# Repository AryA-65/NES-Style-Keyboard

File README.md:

# NES-Style-Keyboard
- - - -

## Notice
- - - -
> [!IMPORTANT]  
> It is always advised that you review the files before ordering, as there may be small issues with the current revision.

## Description
- - - -
A friend of mine wanted to buy a keyboard. I convinced him to let me build him one. I decided to build him a custom 75% keyboard, with some extra features based on his preferences, and styled the color scheme to the popular NES. The whole keyboard, including the case, the main PCB, the switch plate and some of the caps, are custom designed by me.

## Gallery

## Features
- - - -
* Sliding Potentiometer
  * One of my friend's requests was to cater the keyboard more towards CAD design. The only right solution, in my opinion, is a sliding potentiometer for zoom control in apps like Fusion. To zoom using the slider, hold CTRL and move the slider up or down. To scroll horizontally, hold SHIFT and move the slider up or down.
* Rotary Encoder
  * The rotary encoder serves as playback control (play/pause/previous/skip), but also as volume control. If volume control is already mapped by the potentiometer, the encoder can serve to switch audio channels controlled by the potentiometer (ex: switching from the music media channel to the system audio channel)
* Addressable RGB LEDs
  * A total of 6 WS2812b leds are included on the left hand side of the keyboard, right next to the sliding potentiometer. They indicate volume level (if controlled by the potentiometer) and/or caps lock.
* Repairable Design
  * The power supplied to the main PCB comes from a small daughterboard at the back, middle of the case. This daughterboard consists of a 3V3 LDO as well as a fuse. The two PCBs are connected through a standard 15cm (0.5ft) USB-C cable, allowing for easy replacement by the user.
* Unibody Body Case
  * The case for the keyboard is as a unibody case. It is built to offer comfort, whilst keeping a thocky sound (it does sound awesome).
* Hot Swappable Keyswitches
  * Does this need to be explain at this point?

## Default keymaps
```
# Base Layer
[_BASE] = LAYOUT(
        KC_ESC, KC_F1, KC_F2, KC_F3, KC_F4, KC_F5, KC_F6, KC_F7, KC_F8, KC_F9, KC_F10, KC_F11, KC_F12, KC_HOME, KC_END, KC_PAUSE,
        KC_GRV, KC_1, KC_2, KC_3, KC_4, KC_5, KC_6, KC_7, KC_8, KC_9, KC_0, KC_MINS, KC_EQL,                    KC_BSPC, KC_INS,
        KC_TAB,     KC_Q, KC_W, KC_E, KC_R, KC_T, KC_Y, KC_U, KC_I, KC_O, KC_P, KC_LBRC, KC_RBRC,               KC_BSLS, KC_DEL,
        KC_CAPS,        KC_A, KC_S, KC_D, KC_F, KC_G, KC_H, KC_J, KC_K, KC_L, KC_SCLN, KC_QUOT,                 KC_ENT, KC_PGUP,
        KC_LSFT,            KC_Z, KC_X, KC_C, KC_V, KC_B, KC_N, KC_M, KC_COMM, KC_DOT, KC_SLSH, KC_RSFT,        KC_UP, KC_PGDN,
        KC_LCTL,    KC_LGUI,    KC_LALT,            KC_SPC,                   KC_RALT, MO(_FL), KC_RCTL, KC_LEFT, KC_DOWN, KC_RIGHT
    )

#Fn Layer
[_FL] = LAYOUT(
        _______, KC_PWR, KC_F2, KC_BRIU, KC_BRID, KC_F5, KC_MSEL, KC_F7, KC_F8, KC_F9, KC_F10, KC_F11, KC_F12, _______, _______, KC_SLEP,
        _______, _______, _______, _______, _______, _______, _______, _______, _______, _______, _______, UG_SPDD, UG_SPDU,              _______, UG_NEXT,
        _______, _______, _______, _______, _______, _______, _______, _______, _______, _______, _______, _______, _______, _______, UG_PREV,
        _______, _______, _______, _______, _______, _______, _______, _______, _______, _______, _______, _______,     _______, UG_SATU,
        _______, _______, _______, _______, _______, _______, _______, _______, _______, _______, _______, _______,     UG_VALU, UG_SATD,
        _______,    _______,    _______,            _______,                    _______, _______, _______, UG_HUED, UG_VALD, UG_HUEU
    )
```

## Parts List
- - - -
|Part|*Price|*Shipping|Link|
|----|-----------|--------|----|
|Keycaps|$34.18|NaN|[XDA Retro NES Keycaps](https://www.aliexpress.com/item/1005007393936770.html?spm=a2g0o.order_list.order_list_main.25.587f1802SPZi3h)|
|Keyswitches (90pcs)|$32.18|NaN|[MMD Cream Switches (45G)](https://www.aliexpress.com/item/1005007083480212.html?spm=a2g0o.order_list.order_list_main.35.587f1802SPZi3h)|
|Hotswap Sockets (110ps)|$12.21|NaN|[110pcs Kailh Hot-swappable Sockets](https://www.aliexpress.com/item/1005007232040760.html?spm=a2g0o.order_list.order_list_main.30.587f1802SPZi3h)|
|Diodes|$3.17|NaN|[100pcs 1N4148W](https://www.aliexpress.com/item/1005009660071572.html?spm=a2g0o.order_list.order_list_main.20.587f1802SPZi3h)|
|Stabilizers|$25.99|NaN|[Durock Screw in Stabilizers V3 (Black)](https://www.aliexpress.com/item/1005003682325989.html?spm=a2g0o.order_list.order_list_main.10.587f1802SPZi3h)|
|USB-C Cable|$12.64|NaN|[6 inch USB C to USB C Cable (3 Pack)](https://www.amazon.ca/dp/B0CLLRBZDB)|
|BOM|$34.96|$8.00|[BOMs](production_files)|
|Main PCB|$31.20|$43.78**|[Main PCB](production_files/gerbers_to_order_main)|
|Daughterboard|$3.00|$43.78**|[Daughterboard PCB](production_files/gerbers_to_order_secondary)|
|Switch Plate****|$0.00|NaN|[Plate PCB](production_files/gerbers_to_order_plate)|
|Case|$65.13|$43.78**|[Enclosure](production_files/3D_files/)|
|Misc.|$6.50***|$43.78**|[Misc. Parts](production_files/3D_files/)|

Total (excluding import fees): $298.66

*All prices are in CAD, check in your own currency before buying.
**Combined shipping for keyboard and daughterboard PCB, misc. items and enclosure.
***Includes encoder knob, slider handle, power led bar and status bar
****I decided to print the switchplate at home, since it was much cheaper per unit and overall compared to ordering it (price will be updated soon).

## Quickstart
- - - -
### 1) First flash
This step if for first flash, right after assembling your PCBs:
1) Download the UF2 prebuilt firmware in [firmware](firmware/).
2) Connect main board to daughterboard through USB-C intercable (**never connect a USB-C cable directly to the main PCB, it will damage the board**).
3) Press and hold EN button on keyboard.
4) Plug USB-C cable from computer to daughterboard, and let go of the EN button.
5) A USB device will appear in your file explorer, drag and drop UF2 file from your downloads folder into the USB device.
6) If the keyboard automatically resets, the flash was successful. Otherwise, try flashing again.

### 2) Reflash
Since the EN button is on the opposite side of the board and not accessible once the keyboard is assembled, I added a key combo that resets the board and enables flashing new firmware:
1) Press and release right CTRL, ESC, left CTRL and END button at the same time.
2) Drag and drop UF2 firmware from your computer onto the keyboard.
3) If the keyboard automatically resets, the flash was successful. Otherwise, try flashing again (step 1).

## Support
- - - -
Coming Soon

## Tools Used
- - - -
- [Kicad](https://www.kicad.org/)
- [Keyboard Layout Editor](https://www.keyboard-layout-editor.com/#/)
- [Autodesk Fusion](https://www.autodesk.com/products/fusion-360/overview)
- [QMK Firmawre](https://qmk.fm/)

## Legal Notice
- - - -
The software and hardware come as is. It is up to the user to review and make sure that they understand the scope of the project before attempting the project.
[GPL V2 License](LICENSE)

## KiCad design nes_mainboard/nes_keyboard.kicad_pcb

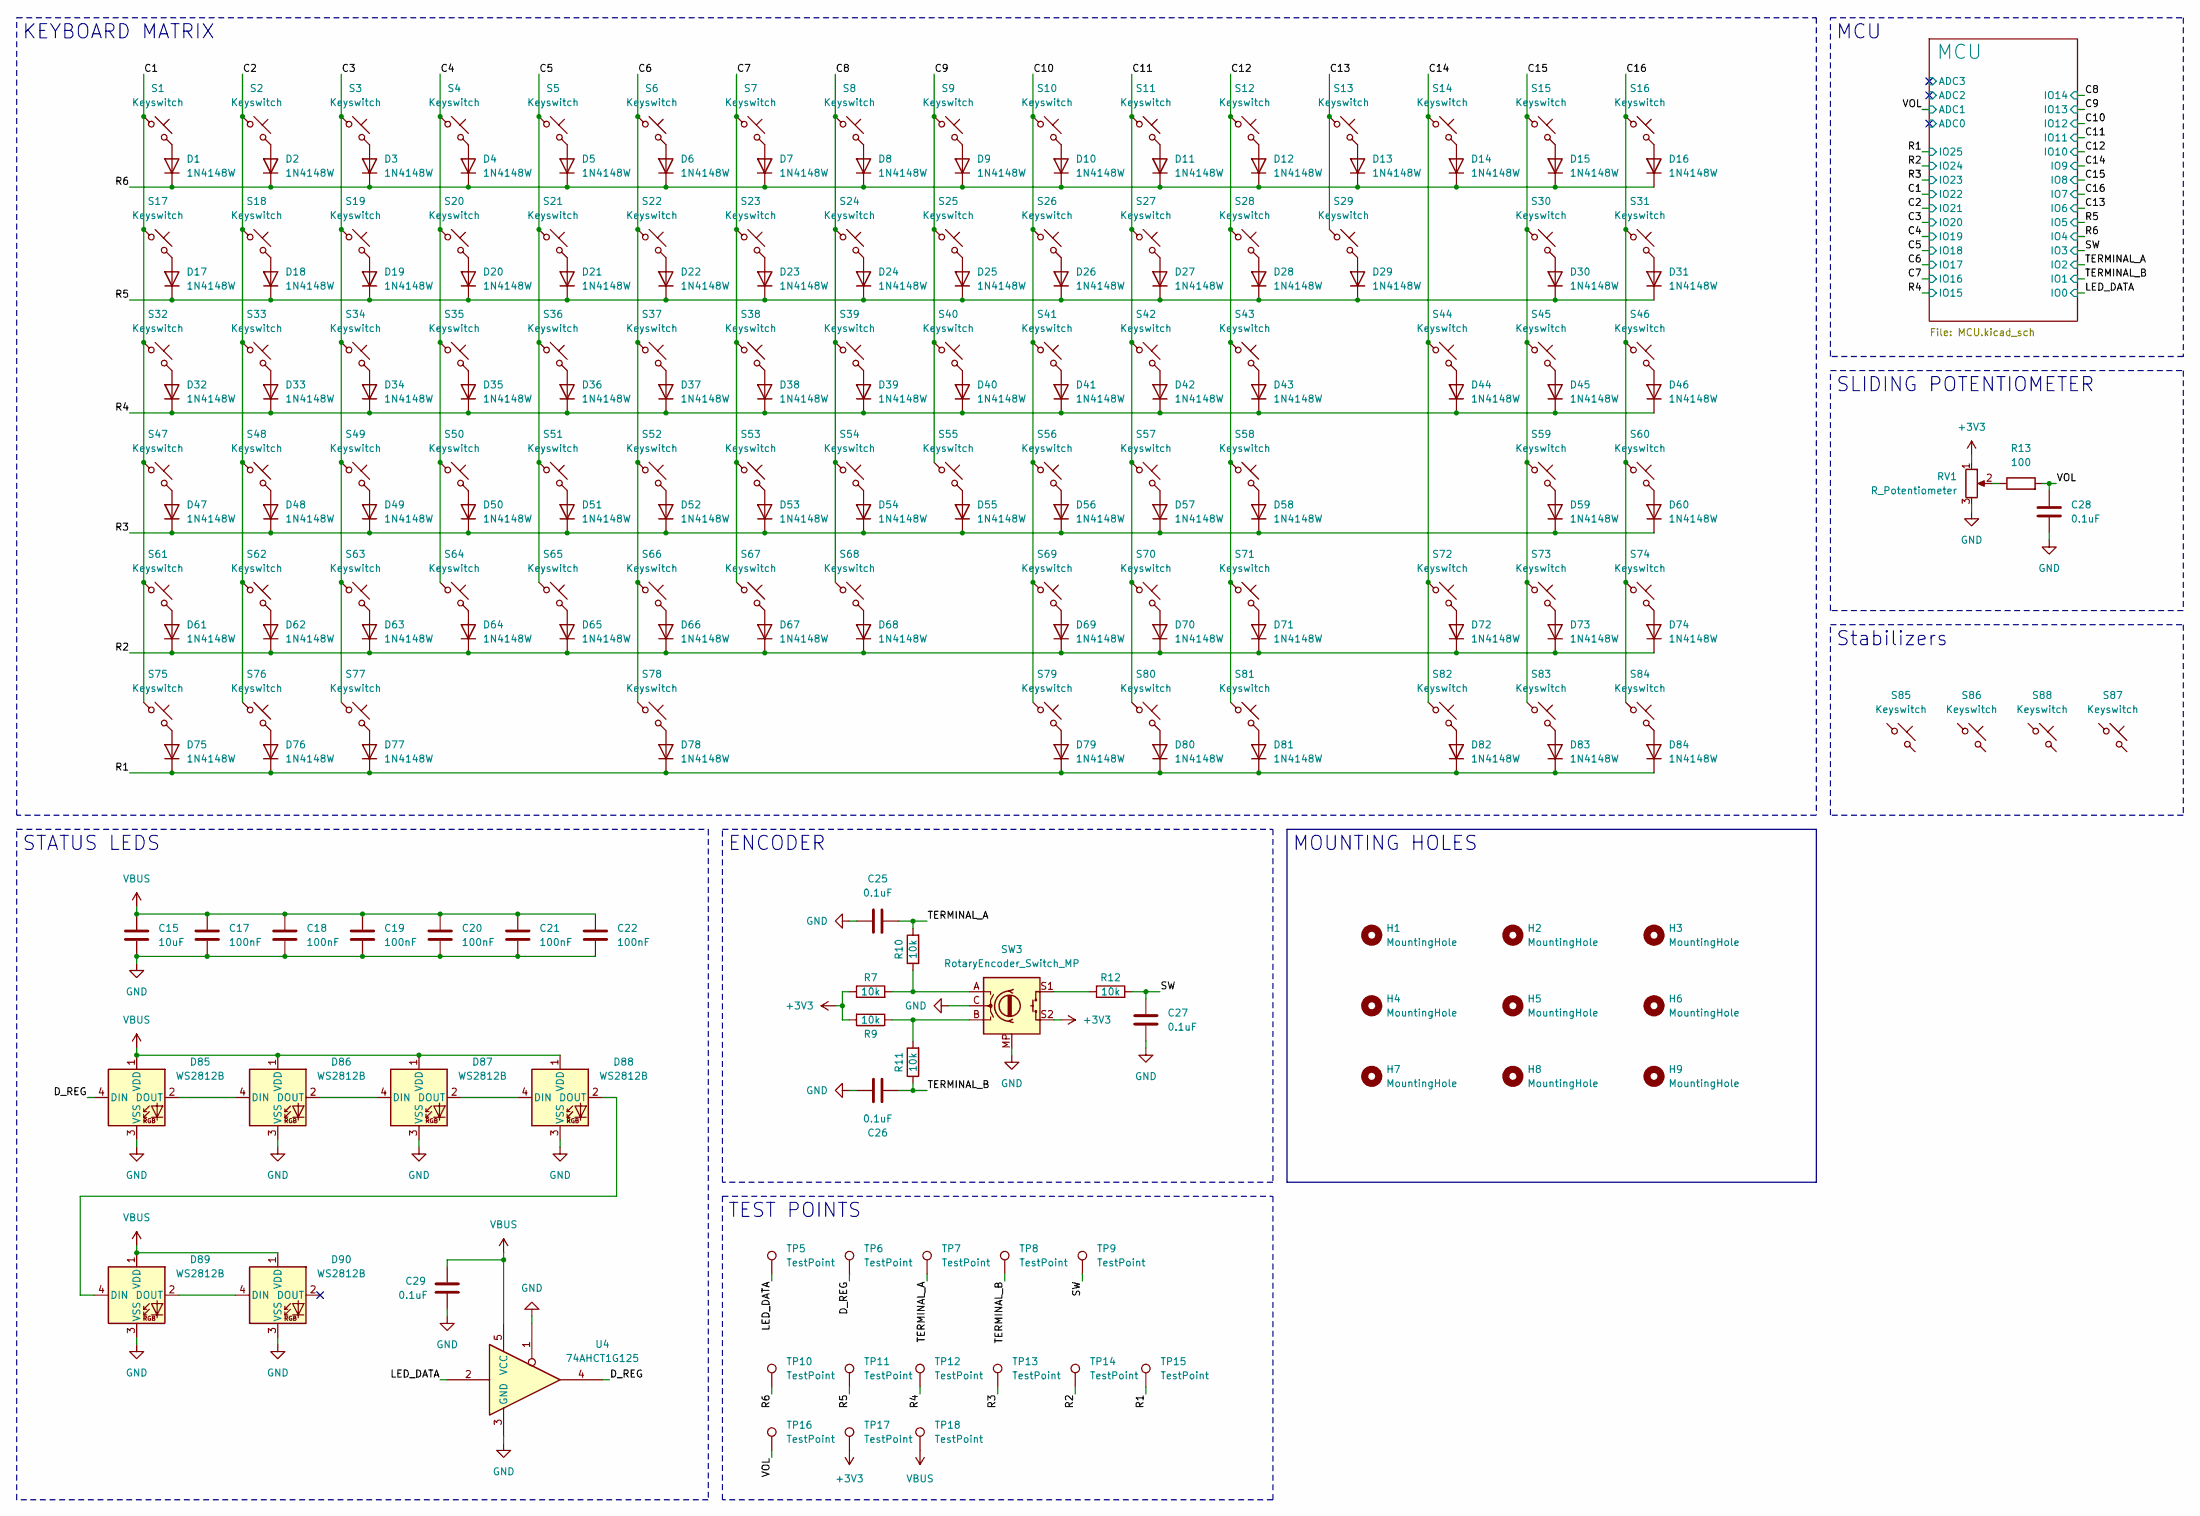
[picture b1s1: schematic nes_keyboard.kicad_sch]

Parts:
C15: 10uF; C_0805_2012Metric; Part Num. CL21A106KOQNNNE
C17, C18, C19, C20, C21, C22: 100nF; C_0603_1608Metric; Part Num. CL10B104KO8NNNC
C25, C26, C27, C28, C29: 0.1uF; C_0402_1005Metric; Part Num. CL05B104KP5NNNC
D1, D2, D3, D4, D5, D6, D7, D8, D9, D10, D11, D12, D13, D14, D15, D16, D17, D18, D19, D20, D21, D22, D23, D24, D25, D26, D27, D28, D29, D30, D31, D32, D33, D34, D35, D36, D37, D38, D39, D40, D41, D42, D43, D44, D45, D46, D47, D48, D49, D50, D51, D52, D53, D54, D55, D56, D57, D58, D59, D60, D61, D62, D63, D64, D65, D66, D67, D68, D69, D70, D71, D72, D73, D74, D75, D76, D77, D78, D79, D80, D81, D82, D83, D84: 1N4148W; D_SOD-123; Part Num. 1N4148W
D85, D86, D87, D88, D89, D90: WS2812B; LED_WS2812B-4020
H1, H2, H3, H4, H5, H6, H7, H8, H9: MountingHole; MountingHole_2.2mm_M2_Pad
R7, R9, R10, R11, R12: 10k; R_0402_1005Metric; Part Num. RMCF0402FT10K0
R13: 100; R_0603_1608Metric; Part Num. RC0603FR-07100RL
RV1: R_Potentiometer; TRIM_PTA6043-2015DPB103; Part Num. PTA6043-2010CIB103
S1, S2, S3, S4, S5, S6, S7, S8, S9, S10, S11, S12, S13, S14, S15, S16, S17, S18, S19, S20, S21, S22, S23, S24, S25, S26, S27, S28, S29, S31, S33, S34, S35, S36, S37, S38, S39, S40, S41, S42, S43, S44, S46, S48, S49, S50, S51, S52, S53, S54, S55, S56, S57, S58, S60, S62, S63, S64, S65, S66, S67, S68, S69, S70, S71, S73, S74, S79, S80, S81, S82, S83, S84: Keyswitch; Hotswap_MX_1.00u
S30: Keyswitch; Hotswap_MX_2.00u
S32, S45: Keyswitch; Hotswap_MX_1.50u
S47, S72: Keyswitch; Hotswap_MX_1.75u
S59, S61: Keyswitch; Hotswap_MX_2.25u
S75, S76, S77: Keyswitch; Hotswap_MX_1.25u
S78: Keyswitch; Hotswap_MX_6.25u
S85, S86, S87: Keyswitch; Stabilizer_Cherry_MX_2.00u
S88: Keyswitch; Stabilizer_Cherry_MX_6.25u
SW3: RotaryEncoder_Switch_MP; RotaryEncoder_Bourns_Vertical_PEC12R-3x17F-Sxxxx; Part Num. PEC12R-4217F-S0024
TP5, TP6, TP7, TP8, TP9, TP10, TP11, TP12, TP13, TP14, TP15, TP16, TP17, TP18: TestPoint; TestPoint_Pad_D1.0mm
U4: 74AHCT1G125; SOT-23-5_HandSoldering; Part Num. SN74AHCT1G125DBVR

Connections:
+3V3: R7.1, R9.2, RV1.1, SW3.S2, TP17.1 (1_1); also elsewhere on the board
/C1: S1.1, S17.1, S32.1, S47.1, S61.1, S75.1; also elsewhere on the board
/C2: S2.1, S18.1, S33.1, S48.1, S62.1, S76.1; also elsewhere on the board
/C3: S3.1, S19.1, S34.1, S49.1, S63.1, S77.1; also elsewhere on the board
/C4: S4.1, S20.1, S35.1, S50.1, S64.1; also elsewhere on the board
/C5: S5.1, S21.1, S36.1, S51.1, S65.1; also elsewhere on the board
/C6: S6.1, S22.1, S37.1, S52.1, S66.1, S78.1; also elsewhere on the board
/C7: S7.1, S23.1, S38.1, S53.1, S67.1; also elsewhere on the board
/C8: S8.1, S24.1, S39.1, S54.1, S68.1; also elsewhere on the board
/C9: S9.1, S25.1, S40.1, S55.1; also elsewhere on the board
/C10: S10.1, S26.1, S41.1, S56.1, S69.1, S79.1; also elsewhere on the board
/C11: S11.1, S27.1, S42.1, S57.1, S70.1, S80.1; also elsewhere on the board
/C12: S12.1, S28.1, S43.1, S58.1, S71.1, S81.1; also elsewhere on the board
/C13: S13.1, S29.1; also elsewhere on the board
/C14: S14.1, S44.1, S72.1, S82.1; also elsewhere on the board
/C15: S15.1, S30.1, S45.1, S59.1, S73.1, S83.1; also elsewhere on the board
/C16: S16.1, S31.1, S46.1, S60.1, S74.1, S84.1; also elsewhere on the board
/D_REG: D85.4 (DIN), TP6.1 (1_1), U4.4
/LED_DATA: TP5.1 (1_1), U4.2; also elsewhere on the board
/R1: D75.1 (K), D76.1 (K), D77.1 (K), D78.1 (K), D79.1 (K), D80.1 (K), D81.1 (K), D82.1 (K), D83.1 (K), D84.1 (K), TP15.1 (1_1); also elsewhere on the board
/R2: D61.1 (K), D62.1 (K), D63.1 (K), D64.1 (K), D65.1 (K), D66.1 (K), D67.1 (K), D68.1 (K), D69.1 (K), D70.1 (K), D71.1 (K), D72.1 (K), D73.1 (K), D74.1 (K), TP14.1 (1_1); also elsewhere on the board
/R3: D47.1 (K), D48.1 (K), D49.1 (K), D50.1 (K), D51.1 (K), D52.1 (K), D53.1 (K), D54.1 (K), D55.1 (K), D56.1 (K), D57.1 (K), D58.1 (K), D59.1 (K), D60.1 (K), TP13.1 (1_1); also elsewhere on the board
/R4: D32.1 (K), D33.1 (K), D34.1 (K), D35.1 (K), D36.1 (K), D37.1 (K), D38.1 (K), D39.1 (K), D40.1 (K), D41.1 (K), D42.1 (K), D43.1 (K), D44.1 (K), D45.1 (K), D46.1 (K), TP12.1 (1_1); also elsewhere on the board
/R5: D17.1 (K), D18.1 (K), D19.1 (K), D20.1 (K), D21.1 (K), D22.1 (K), D23.1 (K), D24.1 (K), D25.1 (K), D26.1 (K), D27.1 (K), D28.1 (K), D29.1 (K), D30.1 (K), D31.1 (K), TP11.1 (1_1); also elsewhere on the board
/R6: D1.1 (K), D2.1 (K), D3.1 (K), D4.1 (K), D5.1 (K), D6.1 (K), D7.1 (K), D8.1 (K), D9.1 (K), D10.1 (K), D11.1 (K), D12.1 (K), D13.1 (K), D14.1 (K), D15.1 (K), D16.1 (K), TP10.1 (1_1); also elsewhere on the board
/SW: C27.1, R12.2, TP9.1 (1_1); also elsewhere on the board
/TERMINAL_A: C25.2, R10.2, TP7.1 (1_1); also elsewhere on the board
/TERMINAL_B: C26.1, R11.1, TP8.1 (1_1); also elsewhere on the board
/VOL: C28.2, R13.2, TP16.1 (1_1); also elsewhere on the board
GND: C15.2, C17.2, C18.2, C19.2, C20.2, C21.2, C22.2, C25.1, C26.2, C27.2, C28.1, C29.2, D85.3 (VSS), D86.3 (VSS), D87.3 (VSS), D88.3 (VSS), D89.3 (VSS), D90.3 (VSS), RV1.3, SW3.C, SW3.MP, U4.1, U4.3 (GND); also elsewhere on the board
unnamed: D1.2 (A), S1.2
unnamed: D2.2 (A), S2.2
unnamed: D3.2 (A), S3.2
unnamed: D4.2 (A), S4.2
unnamed: D5.2 (A), S5.2
unnamed: D6.2 (A), S6.2
unnamed: D7.2 (A), S7.2
unnamed: D8.2 (A), S8.2
unnamed: D9.2 (A), S9.2
unnamed: D10.2 (A), S10.2
unnamed: D11.2 (A), S11.2
unnamed: D12.2 (A), S12.2
unnamed: D13.2 (A), S13.2
unnamed: D14.2 (A), S14.2
unnamed: D15.2 (A), S15.2
unnamed: D16.2 (A), S16.2
unnamed: D17.2 (A), S17.2
unnamed: D18.2 (A), S18.2
unnamed: D19.2 (A), S19.2
unnamed: D20.2 (A), S20.2
unnamed: D21.2 (A), S21.2
unnamed: D22.2 (A), S22.2
unnamed: D23.2 (A), S23.2
unnamed: D24.2 (A), S24.2
unnamed: D25.2 (A), S25.2
unnamed: D26.2 (A), S26.2
unnamed: D27.2 (A), S27.2
unnamed: D28.2 (A), S28.2
unnamed: D29.2 (A), S29.2
unnamed: D30.2 (A), S30.2
unnamed: D31.2 (A), S31.2
unnamed: D32.2 (A), S32.2
unnamed: D33.2 (A), S33.2
unnamed: D34.2 (A), S34.2
unnamed: D35.2 (A), S35.2
unnamed: D36.2 (A), S36.2
unnamed: D37.2 (A), S37.2
unnamed: D38.2 (A), S38.2
unnamed: D39.2 (A), S39.2
unnamed: D40.2 (A), S40.2
unnamed: D41.2 (A), S41.2
unnamed: D42.2 (A), S42.2
unnamed: D43.2 (A), S43.2
unnamed: D44.2 (A), S44.2
unnamed: D45.2 (A), S45.2
unnamed: D46.2 (A), S46.2
unnamed: D47.2 (A), S47.2
unnamed: D48.2 (A), S48.2
unnamed: D49.2 (A), S49.2
unnamed: D50.2 (A), S50.2
unnamed: D51.2 (A), S51.2
unnamed: D52.2 (A), S52.2
unnamed: D53.2 (A), S53.2
unnamed: D54.2 (A), S54.2
unnamed: D55.2 (A), S55.2
unnamed: D56.2 (A), S56.2
unnamed: D57.2 (A), S57.2
unnamed: D58.2 (A), S58.2
unnamed: D59.2 (A), S59.2
unnamed: D60.2 (A), S60.2
unnamed: D61.2 (A), S61.2
unnamed: D62.2 (A), S62.2
unnamed: D63.2 (A), S63.2
unnamed: D64.2 (A), S64.2
unnamed: D65.2 (A), S65.2
unnamed: D66.2 (A), S66.2
unnamed: D67.2 (A), S67.2
unnamed: D68.2 (A), S68.2
unnamed: D69.2 (A), S69.2
unnamed: D70.2 (A), S70.2
unnamed: D71.2 (A), S71.2
unnamed: D72.2 (A), S72.2
unnamed: D73.2 (A), S73.2
unnamed: D74.2 (A), S74.2
unnamed: D75.2 (A), S75.2
unnamed: D76.2 (A), S76.2
unnamed: D77.2 (A), S77.2
unnamed: D78.2 (A), S78.2
unnamed: D79.2 (A), S79.2
unnamed: D80.2 (A), S80.2
unnamed: D81.2 (A), S81.2
unnamed: D82.2 (A), S82.2
unnamed: D83.2 (A), S83.2
unnamed: D84.2 (A), S84.2
unnamed: D85.2 (DOUT), D86.4 (DIN)
unnamed: D86.2 (DOUT), D87.4 (DIN)
unnamed: D87.2 (DOUT), D88.4 (DIN)
unnamed: D88.2 (DOUT), D89.4 (DIN)
unnamed: D89.2 (DOUT), D90.4 (DIN)
unnamed: R7.2, R10.1, SW3.A
unnamed: R9.1, R11.2, SW3.B
unnamed: R12.1, SW3.S1
unnamed: R13.1, RV1.2
VBUS: C15.1, C17.1, C18.1, C19.1, C20.1, C21.1, C22.1, C29.1, D85.1 (VDD), D86.1 (VDD), D87.1 (VDD), D88.1 (VDD), D89.1 (VDD), D90.1 (VDD), TP18.1 (1_1), U4.5 (VCC); also elsewhere on the board

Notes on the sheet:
KEYBOARD MATRIX
MOUNTING HOLES
TEST POINTS
ENCODER
MCU
STATUS LEDS
Stabilizers
SLIDING POTENTIOMETER

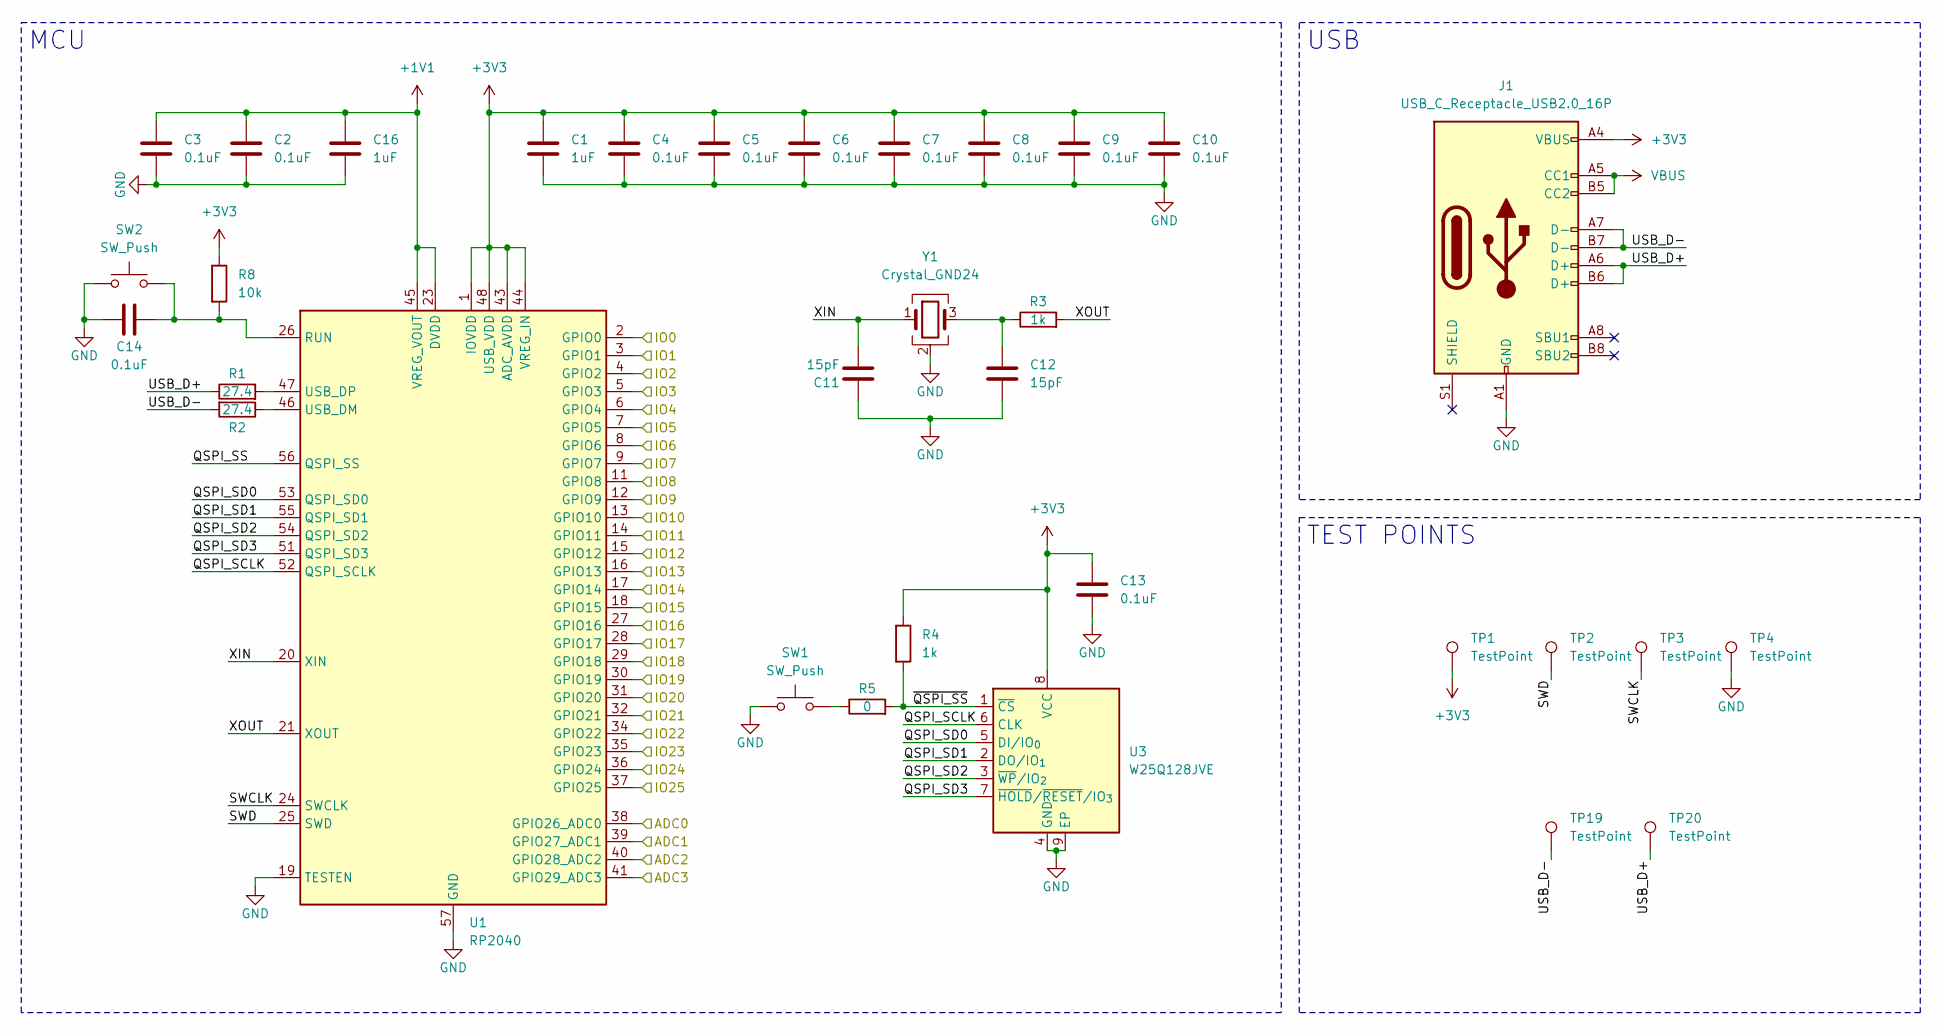
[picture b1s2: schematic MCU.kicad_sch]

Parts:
C1, C16: 1uF; C_0402_1005Metric; Part Num. CL05A105KP5NNNC
C2, C3, C4, C5, C6, C7, C8, C9, C10, C13, C14: 0.1uF; C_0402_1005Metric; Part Num. CL05B104KP5NNNC
C11, C12: 15pF; C_0402_1005Metric; Part Num. 885012005026
J1: USB_C_Receptacle_USB2.0_16P; USB_C_Receptacle_GCT_USB4105-xx-A_16P_TopMnt_Horizontal; Part Num. USB4105-GF-A
R1, R2: 27.4; R_0603_1608Metric; Part Num. RC0603FR-0727R4L
R3: 1k; R_0402_1005Metric; Part Num. RC0402FR-071KL
R4: 1k; R_0603_1608Metric; Part Num. RC0603FR-071KL
R5: 0; R_0603_1608Metric
R8: 10k; R_0603_1608Metric; Part Num. RMCF0603FT10K0
SW1, SW2: SW_Push; SW_SPST_EVQP2_MiddlePushTravel_H2.5mm; Part Num. EVQ-P2402W
TP1, TP2, TP3, TP4, TP19, TP20: TestPoint; TestPoint_Pad_D1.0mm
U1: RP2040; QFN-56-1EP_7x7mm_P0.4mm_EP3.2x3.2mm; Part Num. SC0914(13)
U3: W25Q128JVE; WSON-8-1EP_8x6mm_P1.27mm_EP3.4x4.3mm; Part Num. W25Q128JVEIQ
Y1: Crystal_GND24; Crystal_SMD_3225-4Pin_3.2x2.5mm; Part Num. ABM8-272-T3

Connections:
+1V1: C2.1, C3.1, C16.1, U1.23 (DVDD), U1.45 (VREG_VOUT), U1.50 (DVDD)
+3V3: C1.1, C4.1, C5.1, C6.1, C7.1, C8.1, C9.1, C10.1, C13.1, J1.A4 (VBUS), J1.A9 (VBUS), J1.B4 (VBUS), J1.B9 (VBUS), R4.1, R8.1, TP1.1 (1_1), U1.1 (IOVDD), U1.10 (IOVDD), U1.22 (IOVDD), U1.33 (IOVDD), U1.42 (IOVDD), U1.43 (ADC_AVDD), U1.44 (VREG_IN), U1.48 (USB_VDD), U1.49 (IOVDD), U3.8 (VCC); also elsewhere on the board
/C1: U1.34 (GPIO22); also elsewhere on the board
/C2: U1.32 (GPIO21); also elsewhere on the board
/C3: U1.31 (GPIO20); also elsewhere on the board
/C4: U1.30 (GPIO19); also elsewhere on the board
/C5: U1.29 (GPIO18); also elsewhere on the board
/C6: U1.28 (GPIO17); also elsewhere on the board
/C7: U1.27 (GPIO16); also elsewhere on the board
/C8: U1.17 (GPIO14); also elsewhere on the board
/C9: U1.16 (GPIO13); also elsewhere on the board
/C10: U1.15 (GPIO12); also elsewhere on the board
/C11: U1.14 (GPIO11); also elsewhere on the board
/C12: U1.13 (GPIO10); also elsewhere on the board
/C13: U1.8 (GPIO6); also elsewhere on the board
/C14: U1.12 (GPIO9); also elsewhere on the board
/C15: U1.11 (GPIO8); also elsewhere on the board
/C16: U1.9 (GPIO7); also elsewhere on the board
/LED_DATA: U1.2 (GPIO0); also elsewhere on the board
/MCU/ADC0: U1.38 (GPIO26_ADC0)
/MCU/ADC2: U1.40 (GPIO28_ADC2)
/MCU/ADC3: U1.41 (GPIO29_ADC3)
/MCU/QSPI_SCLK: U1.52 (QSPI_SCLK), U3.6 (CLK)
/MCU/QSPI_SD0: U1.53 (QSPI_SD0), U3.5 (DI/IO_{0})
/MCU/QSPI_SD1: U1.55 (QSPI_SD1), U3.2 (DO/IO_{1})
/MCU/QSPI_SD2: U1.54 (QSPI_SD2), U3.3 (~WP/IO_{2})
/MCU/QSPI_SD3: U1.51 (QSPI_SD3), U3.7 (~HOLD/~RESET/IO_{3})
/MCU/QSPI_SS: U1.56 (QSPI_SS)
/MCU/SWCLK: TP3.1 (1_1), U1.24 (SWCLK)
/MCU/SWD: TP2.1 (1_1), U1.25 (SWD)
/MCU/USB_D+: J1.A6 (D+), J1.B6 (D+), R1.1, TP20.1 (1_1)
/MCU/USB_D-: J1.A7 (D-), J1.B7 (D-), R2.2, TP19.1 (1_1)
/MCU/XIN: C11.2, U1.20 (XIN), Y1.1
/MCU/XOUT: R3.2, U1.21 (XOUT)
/MCU/~QSPI_SS: R4.2, R5.2, U3.1 (~CS)
/R1: U1.37 (GPIO25); also elsewhere on the board
/R2: U1.36 (GPIO24); also elsewhere on the board
/R3: U1.35 (GPIO23); also elsewhere on the board
/R4: U1.18 (GPIO15); also elsewhere on the board
/R5: U1.7 (GPIO5); also elsewhere on the board
/R6: U1.6 (GPIO4); also elsewhere on the board
/SW: U1.5 (GPIO3); also elsewhere on the board
/TERMINAL_A: U1.4 (GPIO2); also elsewhere on the board
/TERMINAL_B: U1.3 (GPIO1); also elsewhere on the board
/VOL: U1.39 (GPIO27_ADC1); also elsewhere on the board
GND: C1.2, C2.2, C3.2, C4.2, C5.2, C6.2, C7.2, C8.2, C9.2, C10.2, C11.1, C12.2, C13.2, C14.1, C16.2, J1.A1 (GND), J1.A12 (GND), J1.B1 (GND), J1.B12 (GND), SW1.1, SW2.1, TP4.1 (1_1), U1.19 (TESTEN), U1.57 (GND), U3.4 (GND), U3.9 (EP), Y1.2 (G), Y1.4 (G); also elsewhere on the board
unnamed: C12.1, R3.1, Y1.3
unnamed: R5.1, SW1.2
unnamed: C14.2, R8.2, SW2.2, U1.26 (RUN)
unnamed: R2.1, U1.46 (USB_DM)
unnamed: R1.2, U1.47 (USB_DP)
VBUS: J1.A5 (CC1), J1.B5 (CC2); also elsewhere on the board

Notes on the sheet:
MCU
USB
TEST POINTS

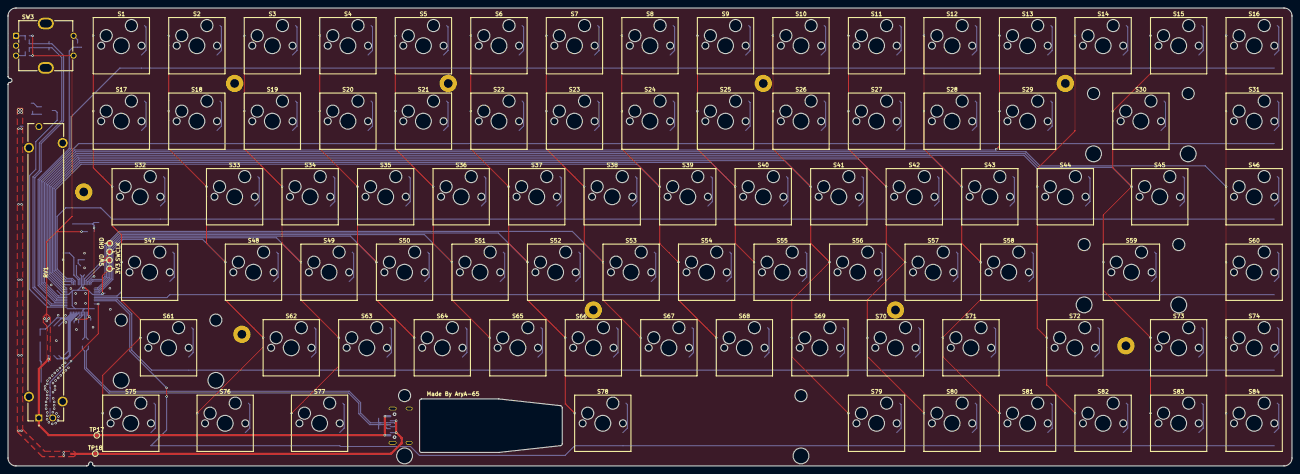
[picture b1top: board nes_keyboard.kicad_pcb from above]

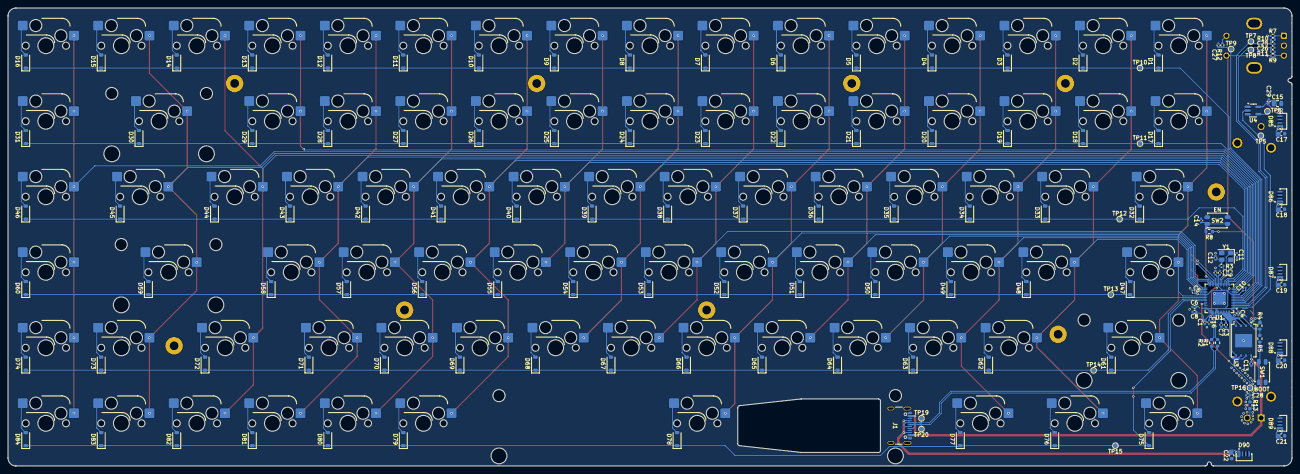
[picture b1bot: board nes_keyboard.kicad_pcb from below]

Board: 2 copper layers, 323.9 x 115.5 mm, 255 parts (150 on the bottom side), 142 nets.

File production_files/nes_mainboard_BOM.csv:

"Reference","Qty","Value","Footprint","Part Num.","Digikey Link"
"C1,C16","2","1uF","Capacitor_SMD:C_0402_1005Metric","CL05A105KP5NNNC","https://www.digikey.ca/en/products/detail/samsung-electro-me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"
"C2,C3,C4,C5,C6,C7,C8,C9,C10,C13,C14,C25,C26,C27,C28,C29","16","0.1uF","Capacitor_SMD:C_0402_1005Metric","CL05B104KP5NNNC","https://www.digikey.ca/en/products/detail/samsung-electro-me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"
"C11,C12","2","15pF","Capacitor_SMD:C_0402_1005Metric","885012005026","https://www.digikey.ca/en/products/detail/w%C3%BCrth-elektro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"
"C15","1","10uF","Capacitor_SMD:C_0805_2012Metric","CL21A106KOQNNNE","https://www.digikey.ca/en/products/detail/samsung-electro-me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"
"C17,C18,C19,C20,C21,C22","6","100nF","Capacitor_SMD:C_0603_1608Metric","CL10B104KO8NNNC","https://www.digikey.ca/en/products/detail/samsung-electro-me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"
"D1,D2,D3,D4,D5,D6,D7,D8,D9,D10,D11,D12,D13,D14,D15,D16,D17,D18,D19,D20,D21,D22,D23,D24,D25,D26,D27,D28,D29,D30,D31,D32,D33,D34,D35,D36,D37,D38,D39,D40,D41,D42,D43,D44,D45,D46,D47,D48,D49,D50,D51,D52,D53,D54,D55,D56,D57,D58,D59,D60,D61,D62,D63,D64,D65,D66,D67,D68,D69,D70,D71,D72,D73,D74,D75,D76,D77,D78,D79,D80,D81,D82,D83,D84","84","1N4148W","Diode_SMD:D_SOD-123","1N4148W","https://www.digikey.ca/en/products/detail/smc-diode-solution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"
"D85,D86,D87,D88,D89,D90","6","WS2812B","LED_WS2812B-4020:LED_WS2812B-4020","","https://www.aliexpress.com/item/1005006254176042.html?spm=a2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"
"J1","1","USB_C_Receptacle_USB2.0_16P","Connector_USB:USB_C_Receptacle_GCT_USB4105-xx-A_16P_TopMnt_Horizontal","USB4105-GF-A","https://www.digikey.ca/en/products/detail/gct/USB4105-GF-A/11198441"
"R1,R2","2","27.4","Resistor_SMD:R_0603_1608Metric","RC0603FR-0727R4L","https://www.digikey.ca/en/products/detail/yageo/RC0603FR-072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"
"R3","1","1k","Resistor_SMD:R_0402_1005Metric","RC0402FR-071KL","https://www.digikey.ca/en/products/detail/yageo/RC0402FR-071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"
"R5","1","1k","Resistor_SMD:R_0603_1608Metric","RC0603FR-071KL","https://www.digikey.ca/en/products/detail/yageo/RC0603FR-071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"
"R7,R9,R10,R11,R12","5","10k","Resistor_SMD:R_0402_1005Metric","RMCF0402FT10K0","https://www.digikey.ca/en/products/detail/stackpole-electron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"
"R8","1","10k","Resistor_SMD:R_0603_1608Metric","RMCF0603FT10K0","https://www.digikey.ca/en/products/detail/stackpole-electron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"
"R13","1","100","Resistor_SMD:R_0603_1608Metric","RC0603FR-07100RL","https://www.digikey.ca/en/products/detail/yageo/RC0603FR-071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"
"RV1","1","R_Potentiometer","PTA6043_2015DPB103:TRIM_PTA6043-2015DPB103","PTA6043-2010CIB103","https://www.digikey.ca/en/products/detail/bourns-inc/PTA6043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"
"S1,S2,S3,S4,S5,S6,S7,S8,S9,S10,S11,S12,S13,S14,S15,S16,S17,S18,S19,S20,S21,S22,S23,S24,S25,S26,S27,S28,S29,S31,S33,S34,S35,S36,S37,S38,S39,S40,S41,S42,S43,S44,S46,S48,S49,S50,S51,S52,S53,S54,S55,S56,S57,S58,S60,S62,S63,S64,S65,S66,S67,S68,S69,S70,S71,S73,S74,S79,S80,S81,S82,S83,S84","73","Keyswitch","ScottoKeebs_Hotswap:Hotswap_MX_1.00u","",""
"S30","1","Keyswitch","ScottoKeebs_Hotswap:Hotswap_MX_2.00u","",""
"S32,S45","2","Keyswitch","ScottoKeebs_Hotswap:Hotswap_MX_1.50u","",""
"S47,S72","2","Keyswitch","ScottoKeebs_Hotswap:Hotswap_MX_1.75u","",""
"S59,S61","2","Keyswitch","ScottoKeebs_Hotswap:Hotswap_MX_2.25u","",""
"S75,S76,S77","3","Keyswitch","ScottoKeebs_Hotswap:Hotswap_MX_1.25u","",""
"S78","1","Keyswitch","ScottoKeebs_Hotswap:Hotswap_MX_6.25u","",""
"S85,S86,S87","3","Keyswitch","PCM_Mounting_Keyboard_Stabilizer:Stabilizer_Cherry_MX_2.00u","",""
"S88","1","Keyswitch","PCM_Mounting_Keyboard_Stabilizer:Stabilizer_Cherry_MX_6.25u","",""
"SW1,SW2","2","SW_Push","Button_Switch_SMD:SW_SPST_EVQP2_MiddlePushTravel_H2.5mm","EVQ-P2402W","https://www.digikey.ca/en/products/detail/panasonic-industry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"
"SW3","1","RotaryEncoder_Switch_MP","Rotary_Encoder:RotaryEncoder_Bourns_Vertical_PEC12R-3x17F-Sxxxx","PEC12R-4217F-S0024","https://www.digikey.ca/en/products/detail/bourns-inc/PEC12R-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"
"TP1,TP2,TP3,TP4,TP5,TP6,TP7,TP8,TP9,TP10,TP11,TP12,TP13,TP14,TP15,TP16,TP19,TP20","18","TestPoint","TestPoint:TestPoint_Pad_D1.0mm","",""
"U1","1","RP2040","Package_DFN_QFN:QFN-56-1EP_7x7mm_P0.4mm_EP3.2x3.2mm_ThermalVias","SC0914(13)","https://www.digikey.ca/en/products/detail/raspberry-pi/SC091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"
"U3","1","W25Q128JVE","Package_SON:WSON-8-1EP_8x6mm_P1.27mm_EP3.4x4.3mm","W25Q128JVEIQ","https://www.digikey.ca/en/products/detail/winbond-electronic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"
"U4","1","74AHCT1G125","Package_TO_SOT_SMD:SOT-23-5_HandSoldering","SN74AHCT1G125DBVR","https://www.digikey.ca/en/products/detail/texas-instruments/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"
"Y1","1","Crystal_GND24","Crystal:Crystal_SMD_3225-4Pin_3.2x2.5mm","ABM8-272-T3","https://www.digikey.ca/en/products/detail/abracon-llc/ABM8-2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"

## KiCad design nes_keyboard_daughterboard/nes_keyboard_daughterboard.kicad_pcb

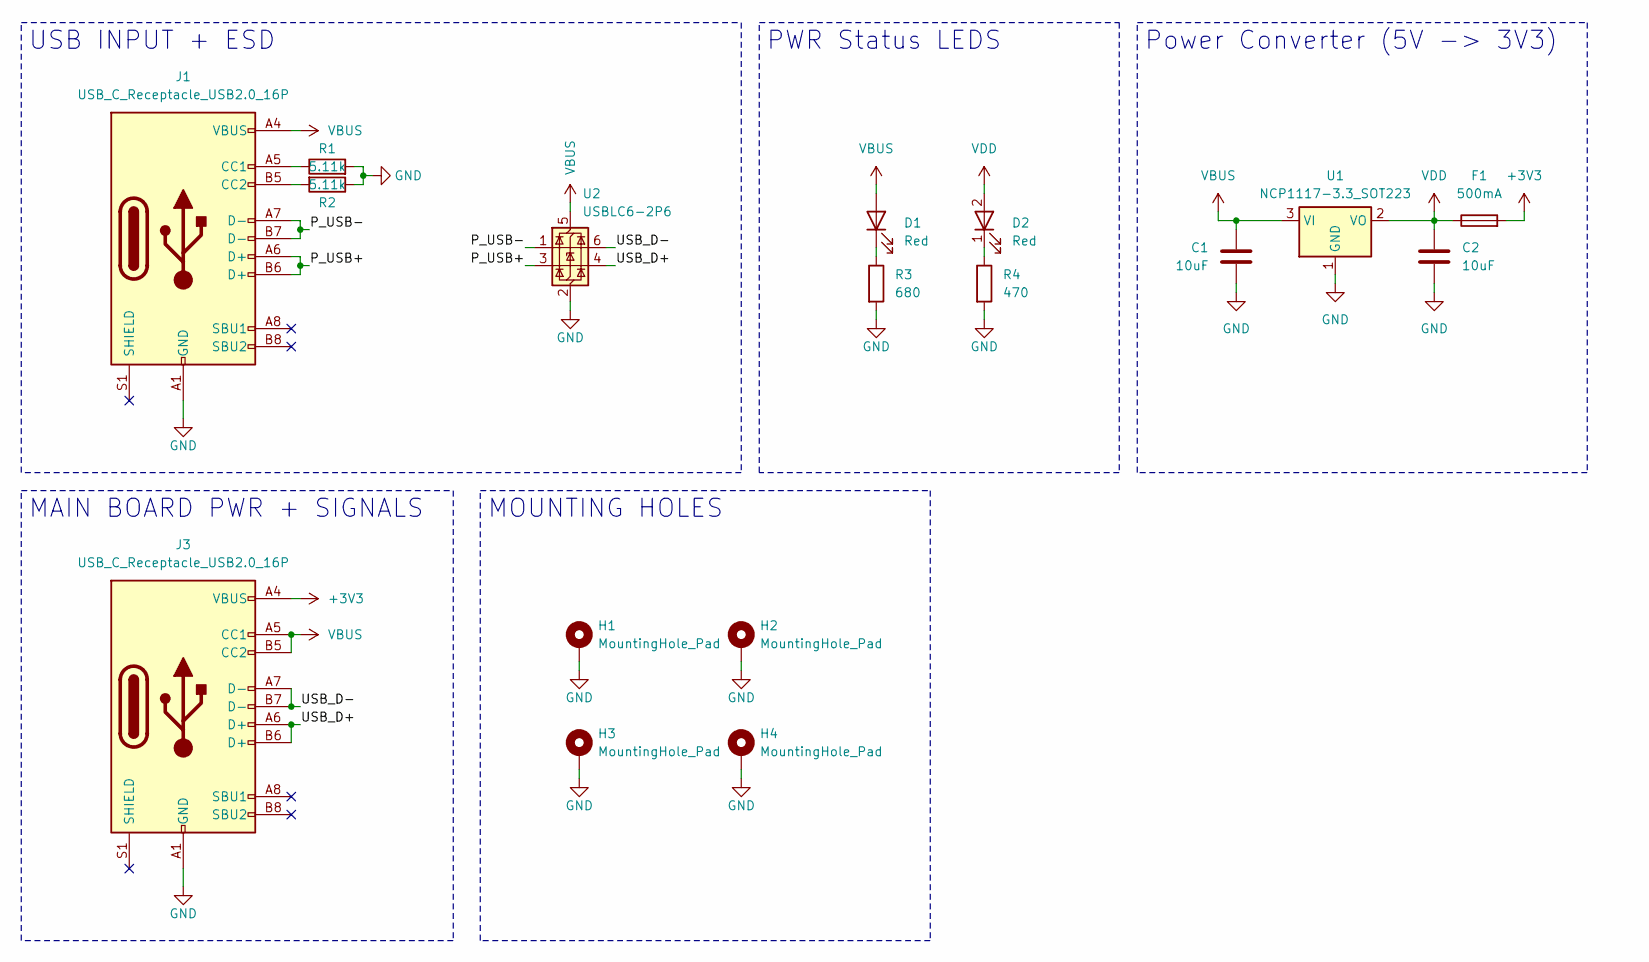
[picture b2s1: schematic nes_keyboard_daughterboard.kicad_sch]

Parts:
C1, C2: 10uF; C_0805_2012Metric; Part Num. CL21A106KOQNNNE
D1, D2: Red; LED_0603_1608Metric_Pad1.05x0.95mm_HandSolder; Part Num. LTST-C191KRKT
F1: 500mA; Fuse_0603_1608Metric; Part Num. ERB-RE0R50V
H1, H2, H3, H4: MountingHole_Pad; MountingHole_2.2mm_M2_DIN965_Pad
J1: USB_C_Receptacle_USB2.0_16P; USB_C_Receptacle_GCT_USB4085; Part Num. USB4085-GF-A
J3: USB_C_Receptacle_USB2.0_16P; USB_C_Receptacle_GCT_USB4105-xx-A_16P_TopMnt_Horizontal; Part Num. USB4105-GF-A
R1, R2: 5.11k; R_0603_1608Metric_Pad0.98x0.95mm_HandSolder; Part Num. RC0603FR-075K1L
R3: 680; R_0603_1608Metric_Pad0.98x0.95mm_HandSolder; Part Num. RC0603JR-07680RL
R4: 470; R_0603_1608Metric_Pad0.98x0.95mm_HandSolder; Part Num. CRGCQ0603F470R
U1: NCP1117-3.3_SOT223; SOT-223-3_TabPin2; Part Num. NCP1117LPST33T3G
U2: USBLC6-2P6; SOT-666; Part Num. USBLC6-2P6

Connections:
+3V3: F1.2, J3.A4 (VBUS), J3.A9 (VBUS), J3.B4 (VBUS), J3.B9 (VBUS)
/P_USB+: J1.A6 (D+), J1.B6 (D+), U2.3 (I/O2)
/P_USB-: J1.A7 (D-), J1.B7 (D-), U2.1 (I/O1)
/USB_D+: J3.A6 (D+), J3.B6 (D+), U2.4 (I/O2)
/USB_D-: J3.A7 (D-), J3.B7 (D-), U2.6 (I/O1)
GND: C1.2, C2.2, H1.1 (1_1), H2.1 (1_1), H3.1 (1_1), H4.1 (1_1), J1.A1 (GND), J1.A12 (GND), J1.B1 (GND), J1.B12 (GND), J3.A1 (GND), J3.A12 (GND), J3.B1 (GND), J3.B12 (GND), R1.2, R2.1, R3.2, R4.2, U1.1 (GND), U2.2 (GND)
unnamed: D1.1 (K), R3.1
unnamed: D2.1 (K), R4.1
unnamed: J1.A5 (CC1), R1.1
unnamed: J1.B5 (CC2), R2.2
VBUS: C1.1, D1.2 (A), J1.A4 (VBUS), J1.A9 (VBUS), J1.B4 (VBUS), J1.B9 (VBUS), J3.A5 (CC1), J3.B5 (CC2), U1.3 (VI), U2.5 (VBUS)
VDD: C2.1, D2.2 (A), F1.1, U1.2 (VO)

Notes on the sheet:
USB INPUT + ESD
PWR Status LEDS
MAIN BOARD PWR + SIGNALS
MOUNTING HOLES
Power Converter (5V -> 3V3)

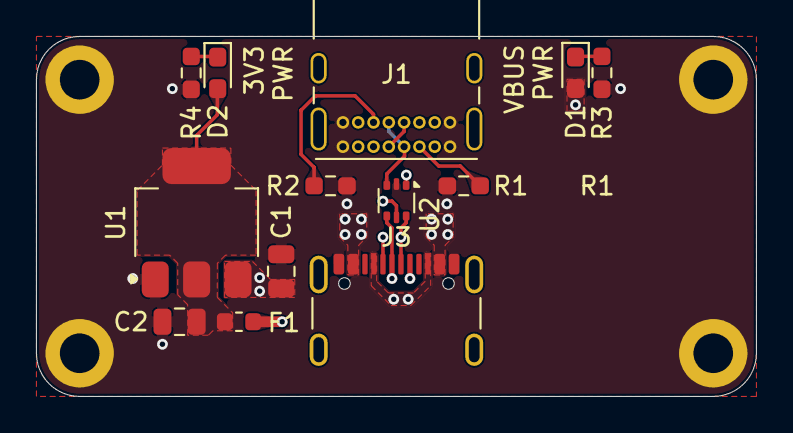
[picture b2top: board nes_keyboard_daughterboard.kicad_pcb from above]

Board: 4 copper layers, 40.0 x 20.0 mm, 17 parts (0 on the bottom side), 12 nets.

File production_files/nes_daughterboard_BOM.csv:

"Reference","Qty","Value","Footprint","Datasheet","Digikey Link","Part Num."
"C1,C2","2","10uF","Capacitor_SMD:C_0805_2012Metric","","https://www.digikey.ca/en/products/detail/samsung-electro-me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","CL21A106KOQNNNE"
"D1,D2","2","Red","LED_SMD:LED_0603_1608Metric_Pad1.05x0.95mm_HandSolder","","https://www.digikey.ca/en/products/detail/liteon/LTST-C191KR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","LTST-C191KRKT"
"F1","1","500mA","Fuse:Fuse_0603_1608Metric","","https://www.digikey.ca/en/products/detail/panasonic-industry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","ERB-RE0R50V"
"J1","1","USB_C_Receptacle_USB2.0_16P","Connector_USB:USB_C_Receptacle_GCT_USB4085","https://www.usb.org/sites/default/files/documents/usb_type-c.zip","https://www.digikey.ca/en/products/detail/gct/USB4085-GF-A/9859662","USB4085-GF-A"
"J3","1","USB_C_Receptacle_USB2.0_16P","Connector_USB:USB_C_Receptacle_GCT_USB4105-xx-A_16P_TopMnt_Horizontal","https://www.usb.org/sites/default/files/documents/usb_type-c.zip","https://www.digikey.ca/en/products/detail/gct/USB4105-GF-A/11198441","USB4105-GF-A"
"R1,R2","2","5.11k","Resistor_SMD:R_0603_1608Metric_Pad0.98x0.95mm_HandSolder","","https://www.digikey.ca/en/products/detail/yageo/RC0603FR-075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","RC0603FR-075K1L"
"R3","1","680","Resistor_SMD:R_0603_1608Metric_Pad0.98x0.95mm_HandSolder","","https://www.digikey.ca/en/products/detail/yageo/RC0603JR-076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","RC0603JR-07680RL  "
"R4","1","470","Resistor_SMD:R_0603_1608Metric_Pad0.98x0.95mm_HandSolder","","https://www.digikey.ca/en/products/detail/te-connectivity-pa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","CRGCQ0603F470R"
"U1","1","NCP1117-3.3_SOT223","Package_TO_SOT_SMD:SOT-223-3_TabPin2","http://www.onsemi.com/pub_link/Collateral/NCP1117-D.PDF","https://www.digikey.ca/en/products/detail/onsemi/NCP1117LPST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","NCP1117LPST33T3G"
"U2","1","USBLC6-2P6","Package_TO_SOT_SMD:SOT-666","https://www.st.com/resource/en/datasheet/usblc6-2.pdf","https://www.digikey.ca/en/products/detail/stmicroelectronics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","USBLC6-2P6"

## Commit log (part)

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2026-05-19 Finished V0.1
2026-05-19 Removed unnecessary files and updated .gitignore
2026-05-27 PCB Modifications (all) - V0.2
2026-06-06 Updated main board + daughterboard layout - V0.3
2026-06-15 Added switchplate - V0.4
2026-06-24 Created and added 3D files - V0.5
